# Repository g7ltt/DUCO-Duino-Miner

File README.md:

# DUCO/Duino-Miner

Here you will find designs for DUCO/DuinoCoin mining rigs based on various microcontrollers. All drawings are in Eagle format.

# 5DN

Uses a Wemos D1 and 5 arduino Nano's. I2C communications between the Wemos and the Nano's with the Wemos handling the network connection via WiFi. An LCD can be added for diagnostic output adn the boards can be "stacked" via the I2C bus. When stacked only a single Wemos is required. Uses code by Ricuan and JK Rolling

# 16-01

Uses 16 ESP-01 modules in one of 2 configurations; I2C Master/Slave mode or WiFi only. In I2C mode uses 1 of the ESP-01's as a Master talking to 15 slaves. wiFi only uses the WiFi radio on all the devices.

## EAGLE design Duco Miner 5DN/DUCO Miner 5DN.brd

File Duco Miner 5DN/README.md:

# Duco Miner 5DN
Arduino Nano (ATMEGA328) and Wemos D1 (ESP8266) based DUCO/Duino Coin miner. Uses a Wemos D1 as an I2C master controlling the 5 Nano I2C slaves. WiFi/Network handled by the Wemos microcontroller.

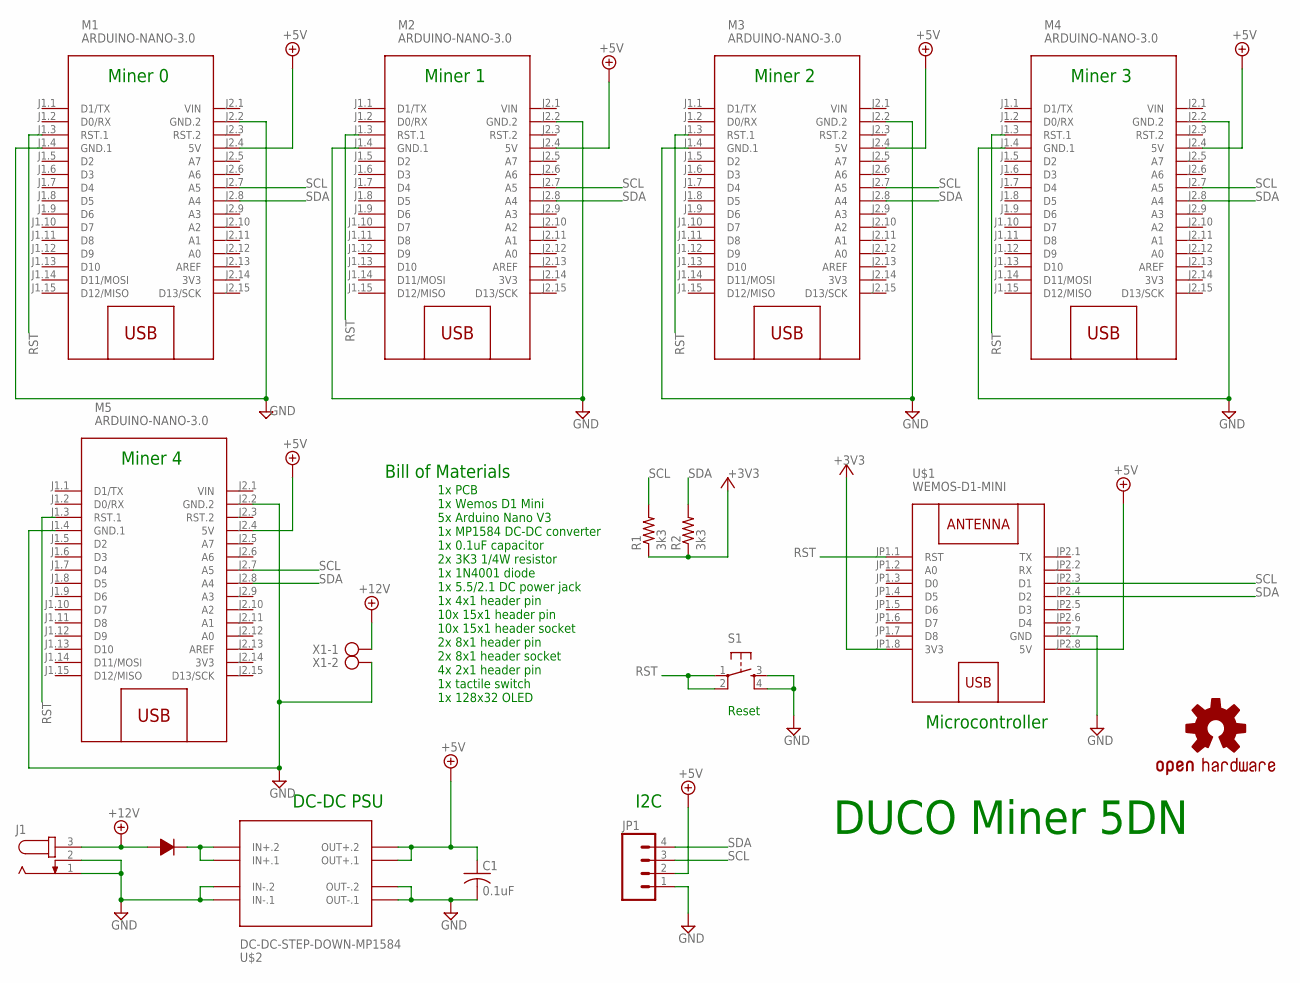
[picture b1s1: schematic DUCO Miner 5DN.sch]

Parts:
C1: 0.1uF; C025-025X050
J1: JACK-PLUG1; SPC4078
JP1: M04PTH; 1X04
LOGO1: OSHW-LOGOS; OSHW-LOGO-S
M1, M2, M3, M4, M5: ARDUINO-NANO-3.0
R1, R2: 3k3; 0204/7
S1: TAC_SWITCHPTH; TACTILE-PTH
U$1: WEMOS-D1-MINI
U$2: DC-DC-STEP-DOWN-MP1584
U$4: 1N4001; DIODE-12.70
X1: AK300/2

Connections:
3V3: M1.J2.14 (3V3), M2.J2.14 (3V3), M3.J2.14 (3V3), M4.J2.14 (3V3), M5.J2.14 (3V3)
+3V3: R1.1, R2.1, U$1.JP1.8 (3V3)
+5V: C1.1, JP1.2, M1.J2.4 (5V), M2.J2.4 (5V), M3.J2.4 (5V), M4.J2.4 (5V), M5.J2.4 (5V), U$1.JP2.8 (5V), U$2.OUT+.1, U$2.OUT+.2
+12V: J1.3, U$4.P$1, X1.1
GND: C1.2, J1.1, J1.2, JP1.1, M1.J1.4 (GND.1), M1.J2.2 (GND.2), M2.J1.4 (GND.1), M2.J2.2 (GND.2), M3.J1.4 (GND.1), M3.J2.2 (GND.2), M4.J1.4 (GND.1), M4.J2.2 (GND.2), M5.J1.4 (GND.1), M5.J2.2 (GND.2), S1.3, S1.4, U$1.JP2.7 (GND), U$2.IN-.1, U$2.IN-.2, U$2.OUT-.1, U$2.OUT-.2, X1.2
unnamed: U$2.IN+.1, U$2.IN+.2, U$4.P$2
RST: M1.J1.3 (RST.1), M2.J1.3 (RST.1), M3.J1.3 (RST.1), M4.J1.3 (RST.1), M5.J1.3 (RST.1), S1.1, S1.2, U$1.JP1.1 (RST)
SCL: JP1.3, M1.J2.7 (A5), M2.J2.7 (A5), M3.J2.7 (A5), M4.J2.7 (A5), M5.J2.7 (A5), R1.2, U$1.JP2.3 (D1)
SDA: JP1.4, M1.J2.8 (A4), M2.J2.8 (A4), M3.J2.8 (A4), M4.J2.8 (A4), M5.J2.8 (A4), R2.2, U$1.JP2.4 (D2)
VIN: M1.J2.1 (VIN), M2.J2.1 (VIN), M3.J2.1 (VIN), M4.J2.1 (VIN), M5.J2.1 (VIN)

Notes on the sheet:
Miner 0
Miner 1
Miner 2
Miner 4
Miner 3
DUCO Miner 5DN
Microcontroller
DC-DC PSU
I2C
Bill of Materials
1x PCB 1x Wemos D1 Mini 5x Arduino Nano V3 1x MP1584 DC-DC converter 1x 0.1uF capacitor 2x 3K3 1/4W resistor 1x 1N4001 diode 1x 5.5/2.1 DC power jack 1x 4x1 header pin 10x 15x1 header pin 10x 15x1 header socket 2x 8x1 header pin 2x 8x1 header socket 4x 2x1 header pin 1x tactile switch 1x 128x32 OLED
Reset

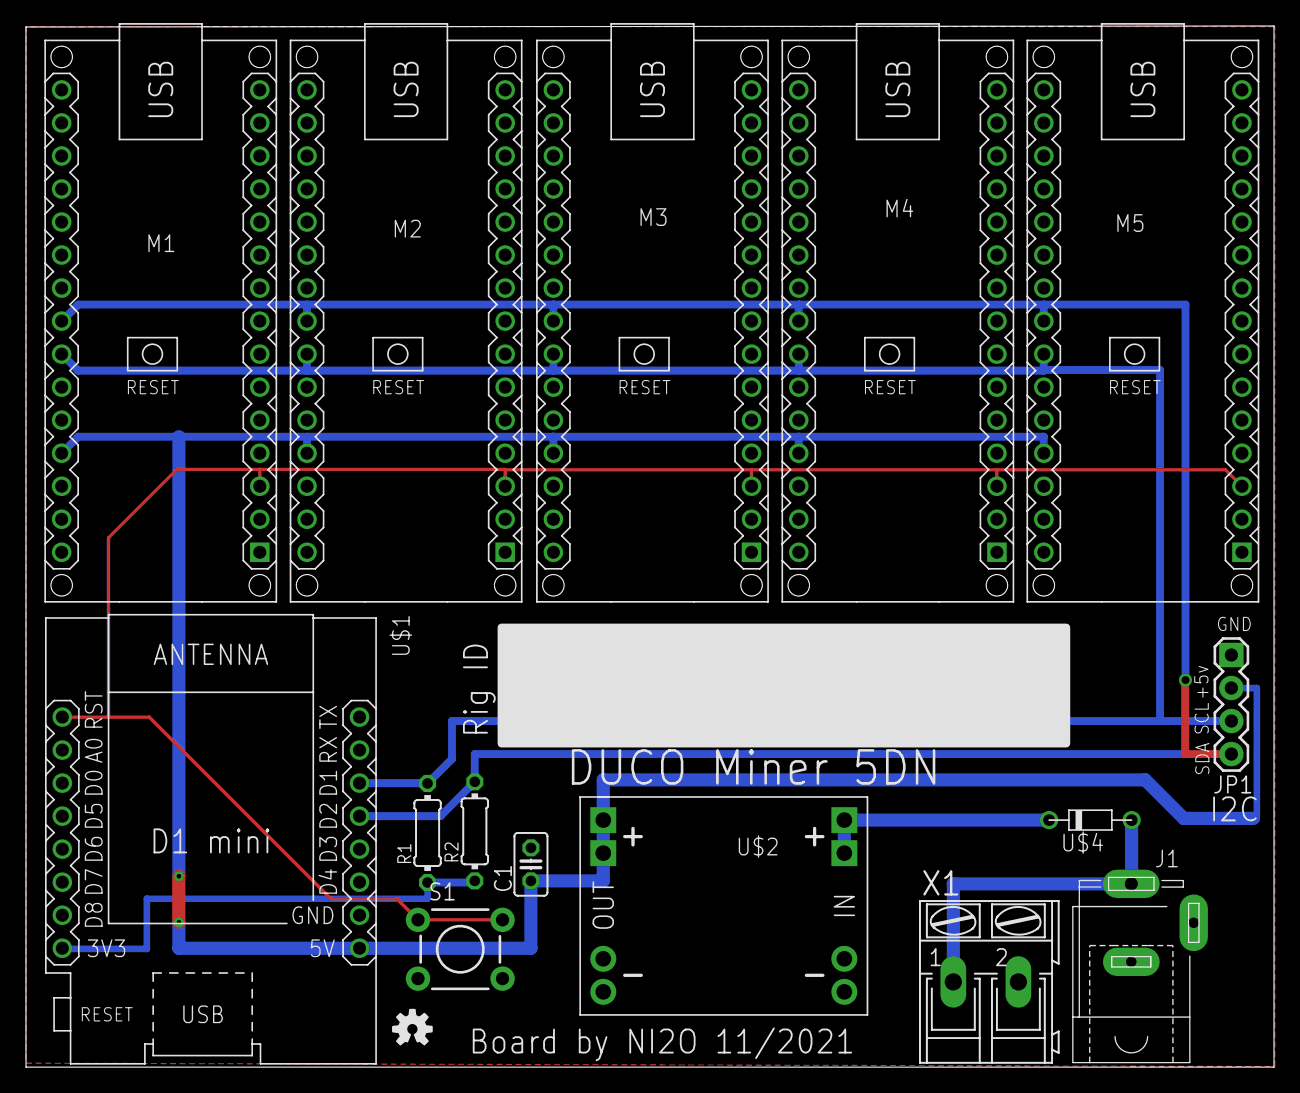
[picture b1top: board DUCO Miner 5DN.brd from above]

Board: 2 copper layers, 96.0 x 80.1 mm, 16 parts (0 on the bottom side), 10 nets.

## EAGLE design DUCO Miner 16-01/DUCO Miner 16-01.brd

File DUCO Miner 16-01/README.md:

# DUCO Miner 16-01

ESP-01 (ESP8266) based DUCO/Duino Coin miner. Uses a gang of ESP-01 Microcontrollers.

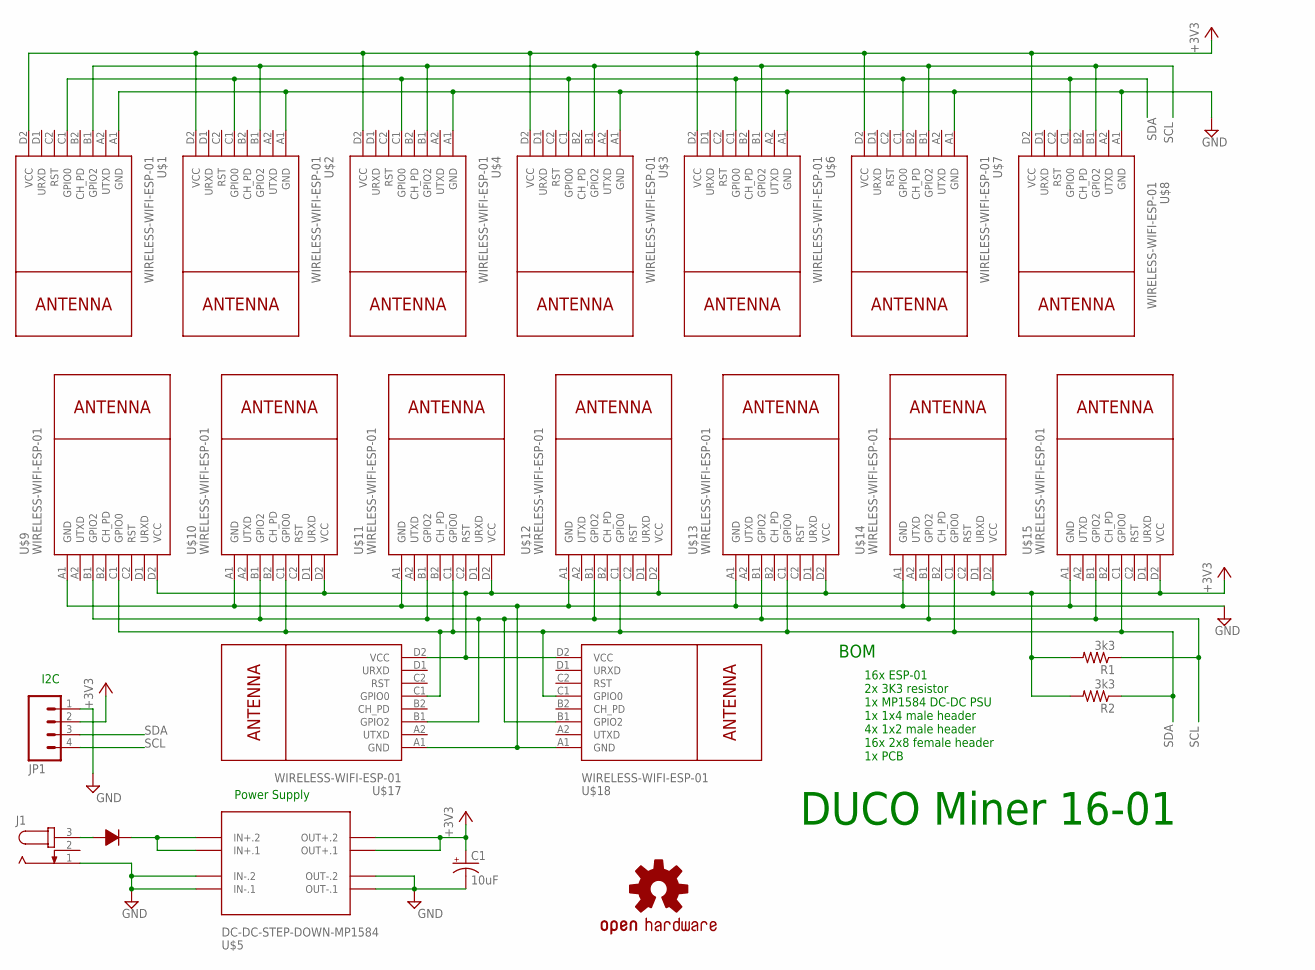
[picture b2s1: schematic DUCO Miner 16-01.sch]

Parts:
C1: 10uF; E2-5
J1: JACK-PLUG0; SPC4077
JP1: M04PTH; 1X04
LOGO1: OSHW-LOGOL; OSHW-LOGO-L
R1, R2: 3k3; 0204/7
U$1, U$2, U$3, U$4, U$6, U$7, U$8, U$9, U$10, U$11, U$12, U$13, U$14, U$15, U$17, U$18: WIRELESS-WIFI-ESP-01
U$5: DC-DC-STEP-DOWN-MP1584
U$16: 1N4001; DIODE-12.70

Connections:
+3V3: C1.+, JP1.2, R1.2, R2.2, U$1.D2 (VCC), U$2.D2 (VCC), U$3.D2 (VCC), U$4.D2 (VCC), U$5.OUT+.1, U$5.OUT+.2, U$6.D2 (VCC), U$7.D2 (VCC), U$8.D2 (VCC), U$9.D2 (VCC), U$10.D2 (VCC), U$11.D2 (VCC), U$12.D2 (VCC), U$13.D2 (VCC), U$14.D2 (VCC), U$15.D2 (VCC), U$17.D2 (VCC), U$18.D2 (VCC)
GND: C1.-, J1.1, JP1.1, U$1.A1 (GND), U$2.A1 (GND), U$3.A1 (GND), U$4.A1 (GND), U$5.IN-.1, U$5.IN-.2, U$5.OUT-.1, U$5.OUT-.2, U$6.A1 (GND), U$7.A1 (GND), U$8.A1 (GND), U$9.A1 (GND), U$10.A1 (GND), U$11.A1 (GND), U$12.A1 (GND), U$13.A1 (GND), U$14.A1 (GND), U$15.A1 (GND), U$17.A1 (GND), U$18.A1 (GND)
unnamed: J1.3, U$16.P$1
unnamed: U$5.IN+.1, U$5.IN+.2, U$16.P$2
SCL: JP1.4, R1.1, U$1.B1 (GPIO2), U$2.B1 (GPIO2), U$3.B1 (GPIO2), U$4.B1 (GPIO2), U$6.B1 (GPIO2), U$7.B1 (GPIO2), U$8.B1 (GPIO2), U$9.B1 (GPIO2), U$10.B1 (GPIO2), U$11.B1 (GPIO2), U$12.B1 (GPIO2), U$13.B1 (GPIO2), U$14.B1 (GPIO2), U$15.B1 (GPIO2), U$17.B1 (GPIO2), U$18.B1 (GPIO2)
SDA: JP1.3, R2.1, U$1.C1 (GPIO0), U$2.C1 (GPIO0), U$3.C1 (GPIO0), U$4.C1 (GPIO0), U$6.C1 (GPIO0), U$7.C1 (GPIO0), U$8.C1 (GPIO0), U$9.C1 (GPIO0), U$10.C1 (GPIO0), U$11.C1 (GPIO0), U$12.C1 (GPIO0), U$13.C1 (GPIO0), U$14.C1 (GPIO0), U$15.C1 (GPIO0), U$17.C1 (GPIO0), U$18.C1 (GPIO0)

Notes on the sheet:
DUCO Miner 16-01
Power Supply
I2C
BOM
16x ESP-01 2x 3K3 resistor 1x MP1584 DC-DC PSU 1x 1x4 male header 4x 1x2 male header 16x 2x8 female header 1x PCB

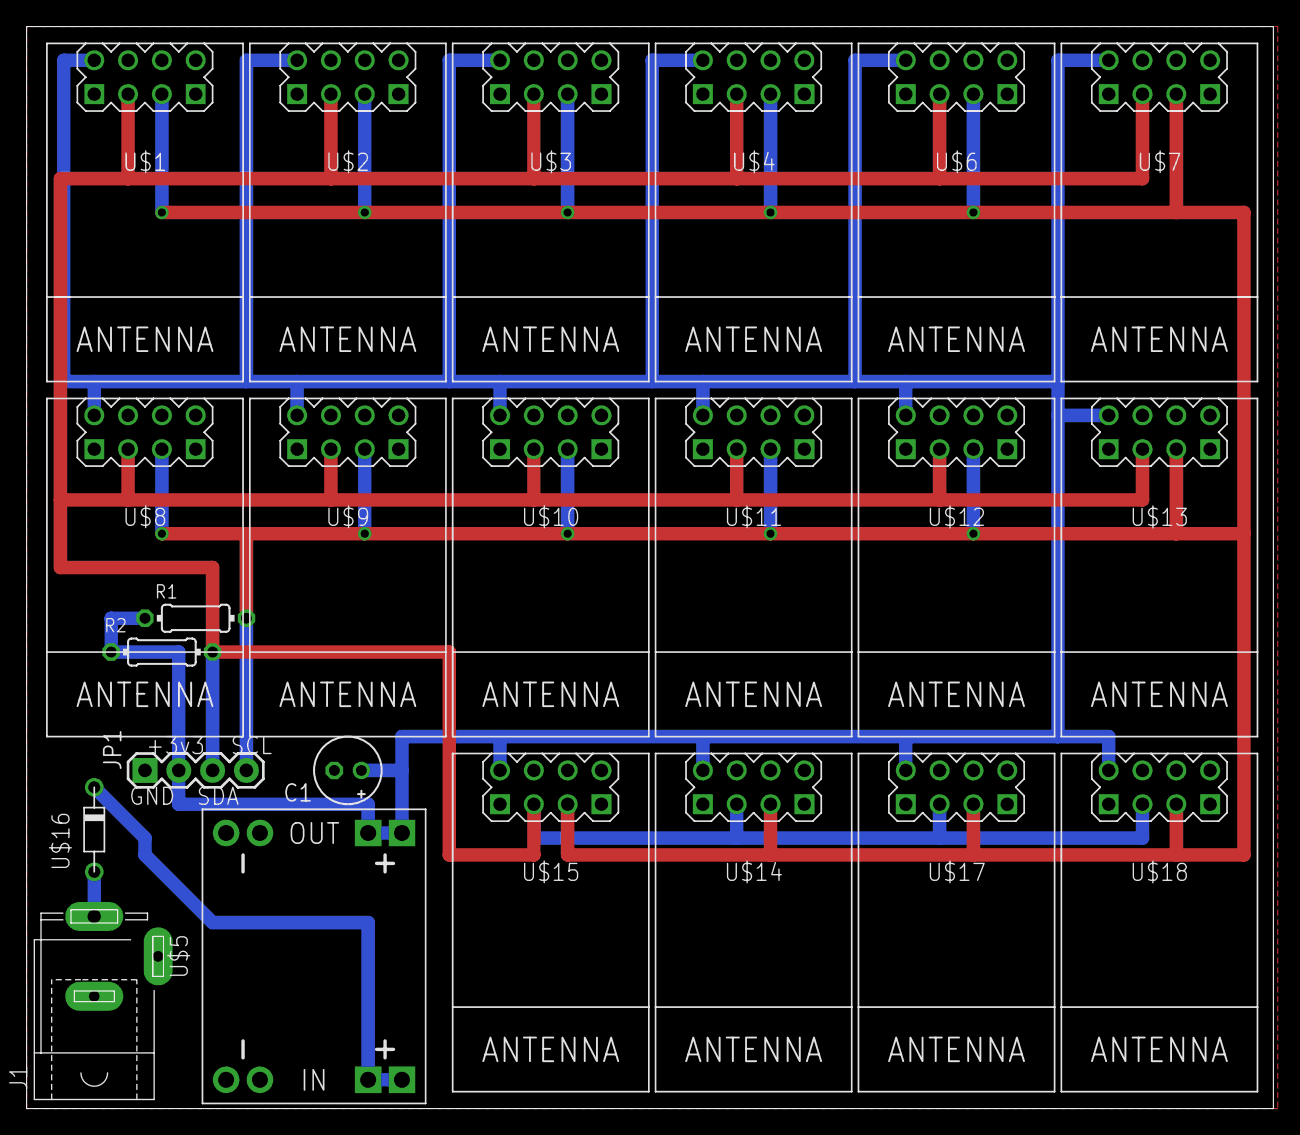
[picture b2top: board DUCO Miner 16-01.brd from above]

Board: 2 copper layers, 93.7 x 81.3 mm, 24 parts (1 on the bottom side), 6 nets.

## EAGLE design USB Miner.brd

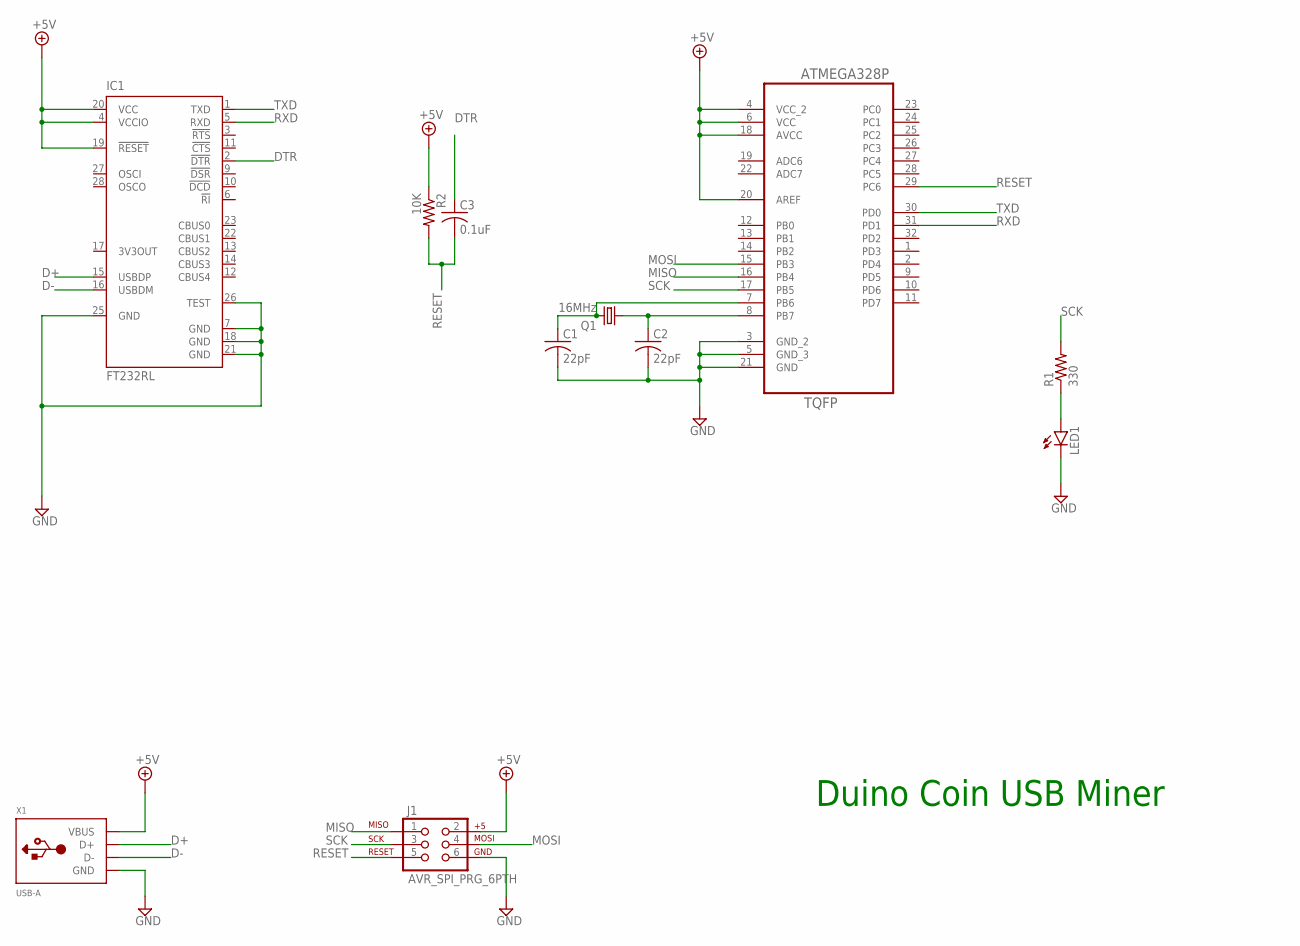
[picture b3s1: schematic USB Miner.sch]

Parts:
C1, C2: 22pF; C0805
C3: 0.1uF; C0805
IC1: FT232RL; SSOP28
J1: AVR_SPI_PRG_6PTH; 2X3
LED1: LEDCHIP-LED0805; CHIP-LED0805
Q1: 16MHz; CTS406
R1: 330; M0805
R2: 10K; M0805
U1: ATMEGA328P-AU; QFP80P900X900X120-32N
X1: USB-A; MOLEX_480371000

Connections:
+5V: IC1.4 (VCCIO), IC1.19 (!RESET), IC1.20 (VCC), J1.2, R2.1, U1.4 (VCC_2), U1.6 (VCC), U1.18 (AVCC), U1.20 (AREF), X1.1 (VBUS)
D+: IC1.15 (USBDP), X1.3 (D+)
D-: IC1.16 (USBDM), X1.2 (D-)
DTR: C3.1, IC1.2 (!DTR)
GND: C1.2, C2.2, IC1.7 (GND), IC1.18 (GND), IC1.21 (GND), IC1.25 (GND), IC1.26 (TEST), J1.6, LED1.C, U1.3 (GND_2), U1.5 (GND_3), U1.21 (GND), X1.4 (GND)
MISO: J1.1, U1.16 (PB4)
MOSI: J1.4, U1.15 (PB3)
unnamed: C2.1, Q1.1, U1.8 (PB7)
unnamed: C1.1, Q1.3 (2), U1.7 (PB6)
unnamed: LED1.A, R1.1
RESET: C3.2, J1.5, R2.2, U1.29 (PC6)
RXD: IC1.5 (RXD), U1.31 (PD1)
SCK: J1.3, R1.2, U1.17 (PB5)
TXD: IC1.1 (TXD), U1.30 (PD0)

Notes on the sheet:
Duino Coin USB Miner

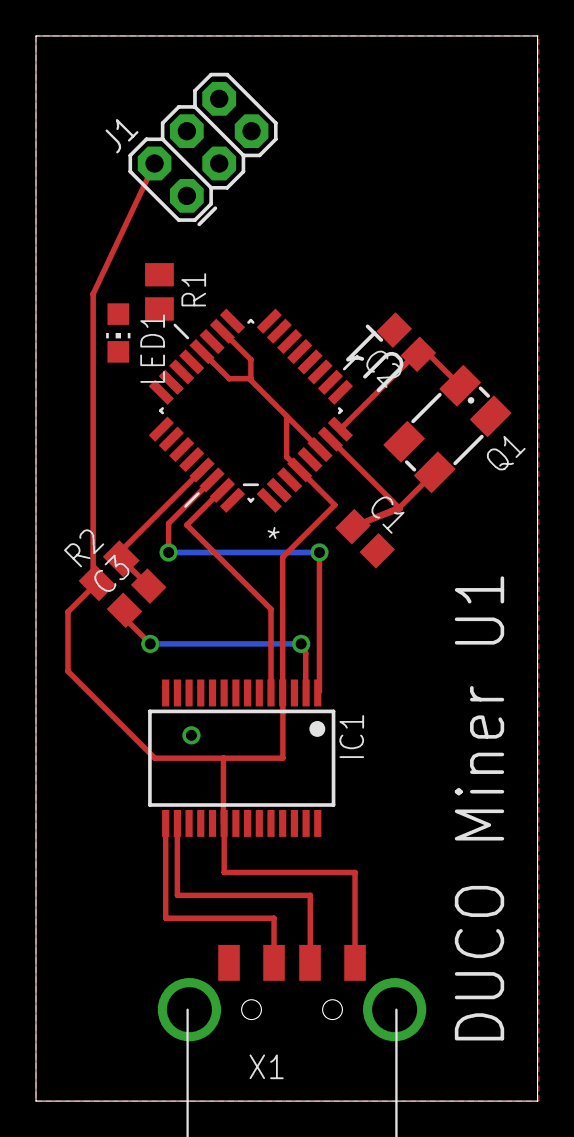
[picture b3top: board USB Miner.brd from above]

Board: 2 copper layers, 27.9 x 59.2 mm, 11 parts (0 on the bottom side), 14 nets.

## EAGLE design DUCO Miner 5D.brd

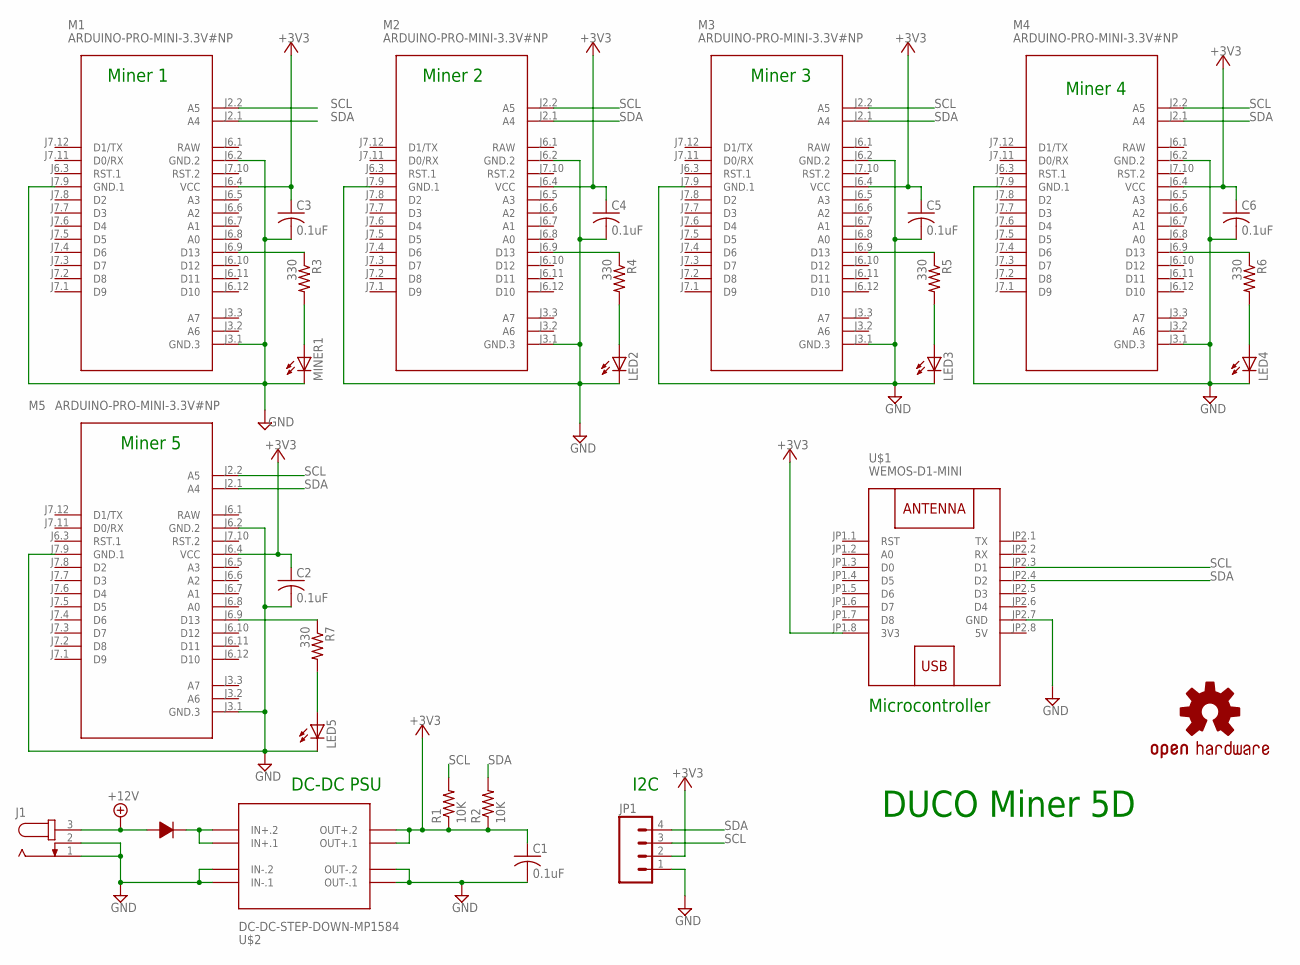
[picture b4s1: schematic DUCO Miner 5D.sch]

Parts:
C1, C2, C3, C4, C5, C6: 0.1uF; C025-025X050
J1: JACK-PLUG1; SPC4078
JP1: M04PTH; 1X04
LED2, LED3, LED4, LED5: LED3MM
LOGO1: OSHW-LOGOS; OSHW-LOGO-S
M1, M2, M3, M4, M5: ARDUINO-PRO-MINI-3.3V#NP; ARDUINO-PRO-MINI#NP
MINER1: LED3MM
R1, R2: 10K; 0204/7
R3, R4, R5, R6, R7: 330; 0204/7
U$1: WEMOS-D1-MINI
U$2: DC-DC-STEP-DOWN-MP1584
U$4: 1N4001; DIODE-12.70

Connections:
5V: U$1.JP2.8 (5V)
+3V3: C1.1, C2.1, C3.1, C4.1, C5.1, C6.1, JP1.2, M1.J6.4 (VCC), M2.J6.4 (VCC), M3.J6.4 (VCC), M4.J6.4 (VCC), M5.J6.4 (VCC), R1.1, R2.1, U$1.JP1.8 (3V3), U$2.OUT+.1, U$2.OUT+.2
+12V: J1.3, U$4.P$1
GND: C1.2, C2.2, C3.2, C4.2, C5.2, C6.2, J1.1, J1.2, JP1.1, LED2.K (C), LED3.K (C), LED4.K (C), LED5.K (C), M1.J3.1 (GND.3), M1.J6.2 (GND.2), M1.J7.9 (GND.1), M2.J3.1 (GND.3), M2.J6.2 (GND.2), M2.J7.9 (GND.1), M3.J3.1 (GND.3), M3.J6.2 (GND.2), M3.J7.9 (GND.1), M4.J3.1 (GND.3), M4.J6.2 (GND.2), M4.J7.9 (GND.1), M5.J3.1 (GND.3), M5.J6.2 (GND.2), M5.J7.9 (GND.1), MINER1.K (C), U$1.JP2.7 (GND), U$2.IN-.1, U$2.IN-.2, U$2.OUT-.1, U$2.OUT-.2
unnamed: U$2.IN+.1, U$2.IN+.2, U$4.P$2
unnamed: M1.J6.9 (D13), R3.1
unnamed: MINER1.A, R3.2
unnamed: M2.J6.9 (D13), R4.1
unnamed: LED2.A, R4.2
unnamed: M3.J6.9 (D13), R5.1
unnamed: LED3.A, R5.2
unnamed: M4.J6.9 (D13), R6.1
unnamed: LED4.A, R6.2
unnamed: M5.J6.9 (D13), R7.1
unnamed: LED5.A, R7.2
RAW: M1.J6.1 (RAW), M2.J6.1 (RAW), M3.J6.1 (RAW), M4.J6.1 (RAW), M5.J6.1 (RAW)
SCL: JP1.3, M1.J2.2 (A5), M2.J2.2 (A5), M3.J2.2 (A5), M4.J2.2 (A5), M5.J2.2 (A5), R1.2, U$1.JP2.3 (D1)
SDA: JP1.4, M1.J2.1 (A4), M2.J2.1 (A4), M3.J2.1 (A4), M4.J2.1 (A4), M5.J2.1 (A4), R2.2, U$1.JP2.4 (D2)

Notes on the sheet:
Miner 1
Miner 2
Miner 3
Miner 4
Miner 5
DUCO Miner 5D
Microcontroller
DC-DC PSU
I2C

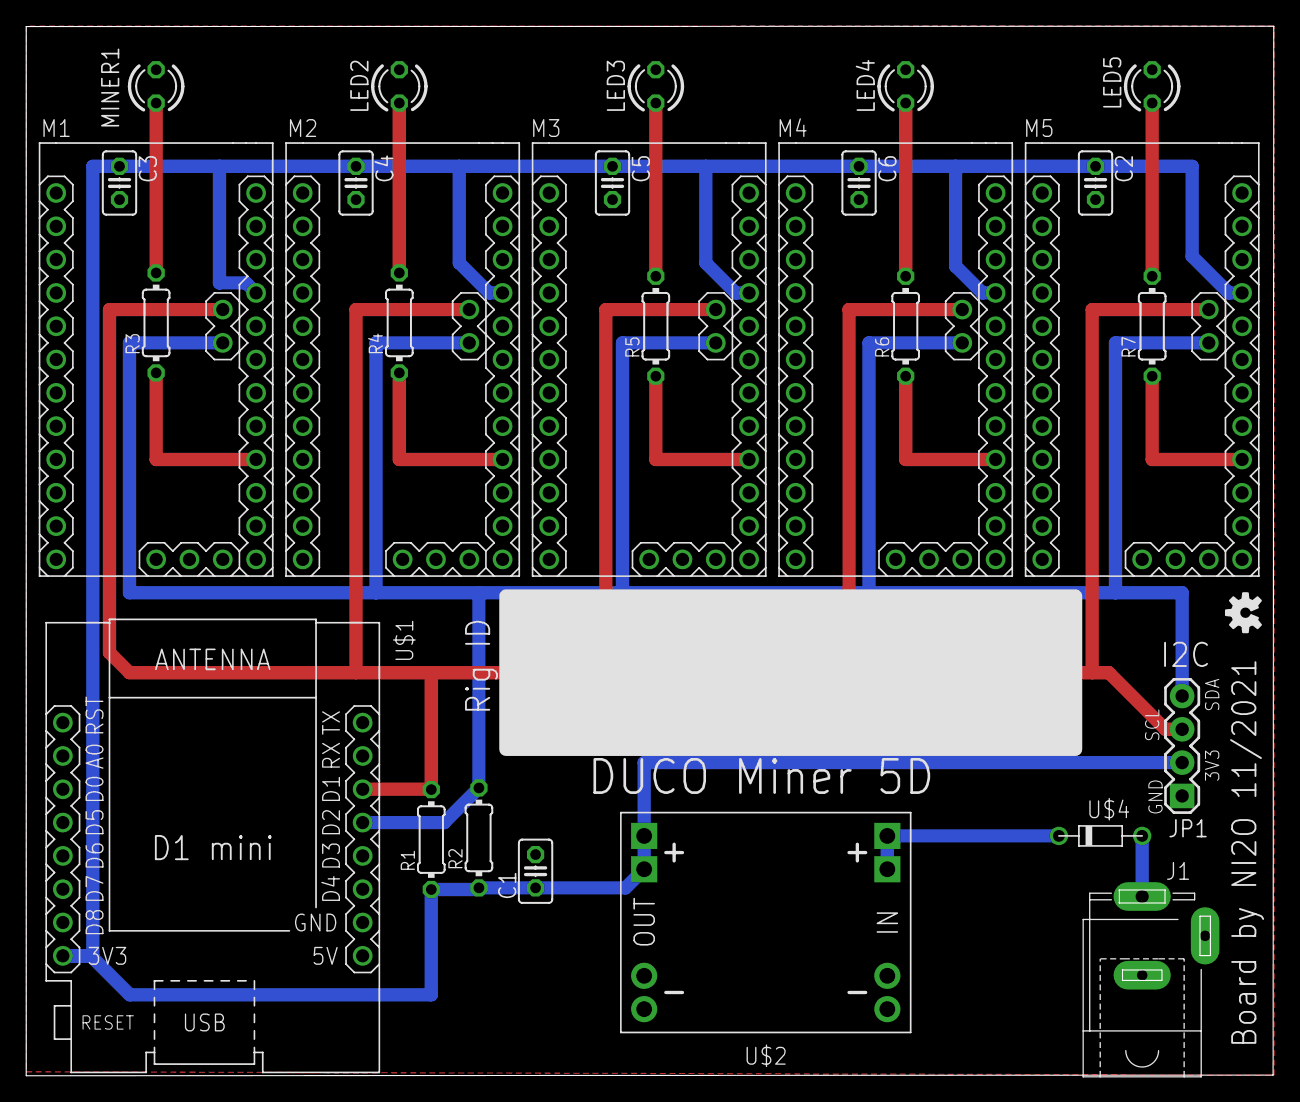
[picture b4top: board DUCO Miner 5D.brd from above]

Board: 2 copper layers, 95.1 x 80.0 mm, 29 parts (0 on the bottom side), 17 nets.

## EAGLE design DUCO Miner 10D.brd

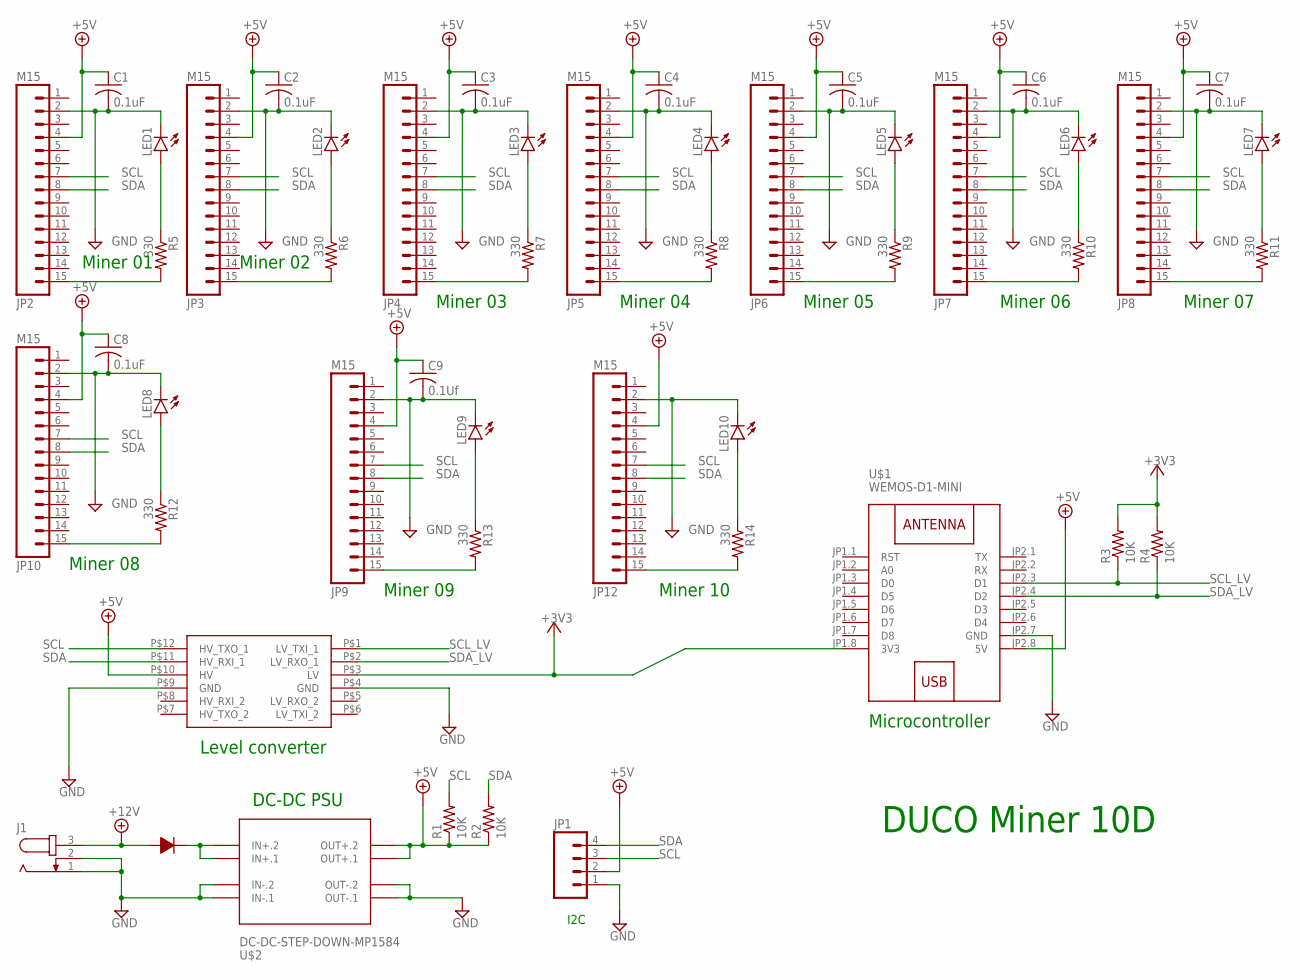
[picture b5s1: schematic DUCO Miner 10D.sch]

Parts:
C1, C2, C3, C4, C5, C6, C7, C8: 0.1uF; C025-025X050
C9: 0.1Uf; C025-025X050
J1: JACK-PLUG1; SPC4078
JP1: M04PTH; 1X04
JP2, JP3, JP4, JP5, JP6, JP7, JP8, JP9, JP10, JP12: M15; 1X15
LED1, LED2, LED3, LED4, LED5, LED6, LED7, LED8, LED9, LED10: LED3MM
R1, R2, R3, R4: 10K; 0204/7
R5, R6, R7, R8, R9, R10, R11, R12, R13, R14: 330; 0204/7
U$1: WEMOS-D1-MINI
U$2: DC-DC-STEP-DOWN-MP1584
U$3: LOGIC_LEVEL_CONVERTER
U$4: 1N4001; DIODE-12.70

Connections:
+3V3: R3.2, R4.2, U$1.JP1.8 (3V3), U$3.P$3 (LV)
+5V: C1.1, C2.1, C3.1, C4.1, C5.1, C6.1, C7.1, C8.1, C9.1, JP1.2, JP2.4, JP3.4, JP4.4, JP5.4, JP6.4, JP7.4, JP8.4, JP9.4, JP10.4, JP12.4, R1.1, R2.1, U$1.JP2.8 (5V), U$2.OUT+.1, U$2.OUT+.2, U$3.P$10 (HV)
+12V: J1.3, U$4.P$1
GND: C1.2, C2.2, C3.2, C4.2, C5.2, C6.2, C7.2, C8.2, C9.2, J1.1, J1.2, JP1.1, JP2.2, JP3.2, JP4.2, JP5.2, JP6.2, JP7.2, JP8.2, JP9.2, JP10.2, JP12.2, LED1.K (C), LED2.K (C), LED3.K (C), LED4.K (C), LED5.K (C), LED6.K (C), LED7.K (C), LED8.K (C), LED9.K (C), LED10.K (C), U$1.JP2.7 (GND), U$2.IN-.1, U$2.IN-.2, U$2.OUT-.1, U$2.OUT-.2, U$3.P$4 (GND), U$3.P$9 (GND)
unnamed: JP2.15, R5.2
unnamed: U$2.IN+.1, U$2.IN+.2, U$4.P$2
unnamed: LED1.A, R5.1
unnamed: JP12.15, R14.2
unnamed: JP3.15, R6.2
unnamed: LED2.A, R6.1
unnamed: JP9.15, R13.2
unnamed: JP4.15, R7.2
unnamed: LED3.A, R7.1
unnamed: JP10.15, R12.2
unnamed: JP5.15, R8.2
unnamed: LED4.A, R8.1
unnamed: JP6.15, R9.2
unnamed: LED5.A, R9.1
unnamed: JP7.15, R10.2
unnamed: LED6.A, R10.1
unnamed: LED8.A, R12.1
unnamed: JP8.15, R11.2
unnamed: LED7.A, R11.1
unnamed: LED9.A, R13.1
unnamed: LED10.A, R14.1
SCL: JP1.3, JP2.7, JP3.7, JP4.7, JP5.7, JP6.7, JP7.7, JP8.7, JP9.7, JP10.7, JP12.7, R1.2, U$3.P$12 (HV_TXO_1)
SCL_LV: R3.1, U$1.JP2.3 (D1), U$3.P$1 (LV_TXI_1)
SDA: JP1.4, JP2.8, JP3.8, JP4.8, JP5.8, JP6.8, JP7.8, JP8.8, JP9.8, JP10.8, JP12.8, R2.2, U$3.P$11 (HV_RXI_1)
SDA_LV: R4.1, U$1.JP2.4 (D2), U$3.P$2 (LV_RXO_1)

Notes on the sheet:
Miner 01
DUCO Miner 10D
Level converter
Microcontroller
DC-DC PSU
Miner 02
I2C
Miner 03
Miner 04
Miner 05
Miner 06
Miner 07
Miner 08
Miner 09
Miner 10

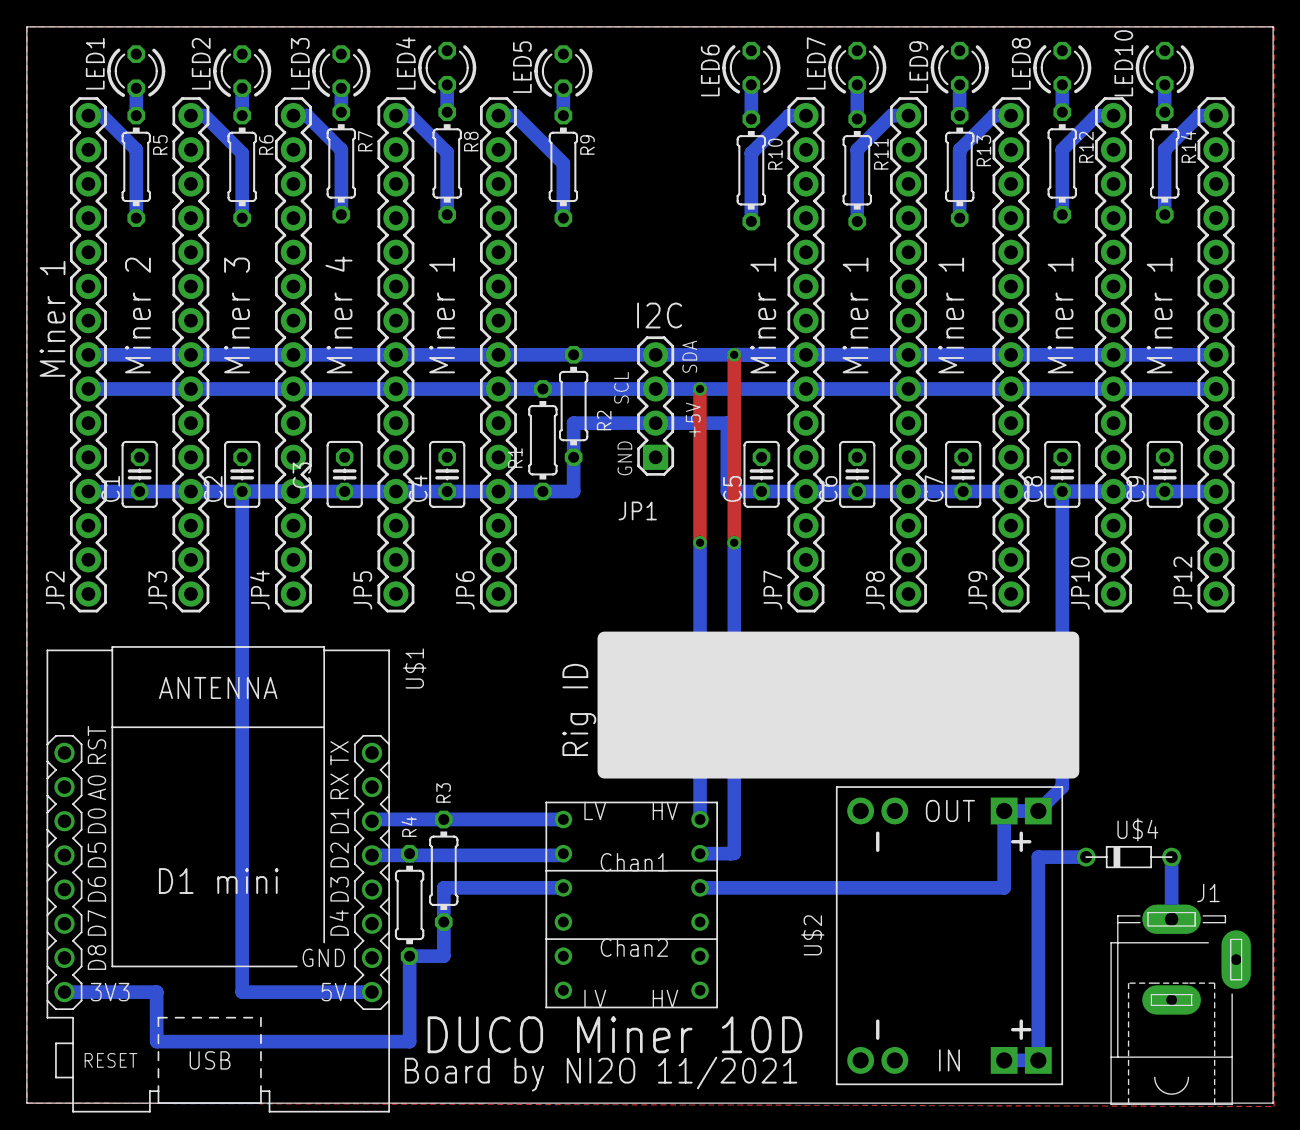
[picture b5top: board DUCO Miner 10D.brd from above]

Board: 2 copper layers, 92.6 x 80.0 mm, 49 parts (0 on the bottom side), 29 nets.

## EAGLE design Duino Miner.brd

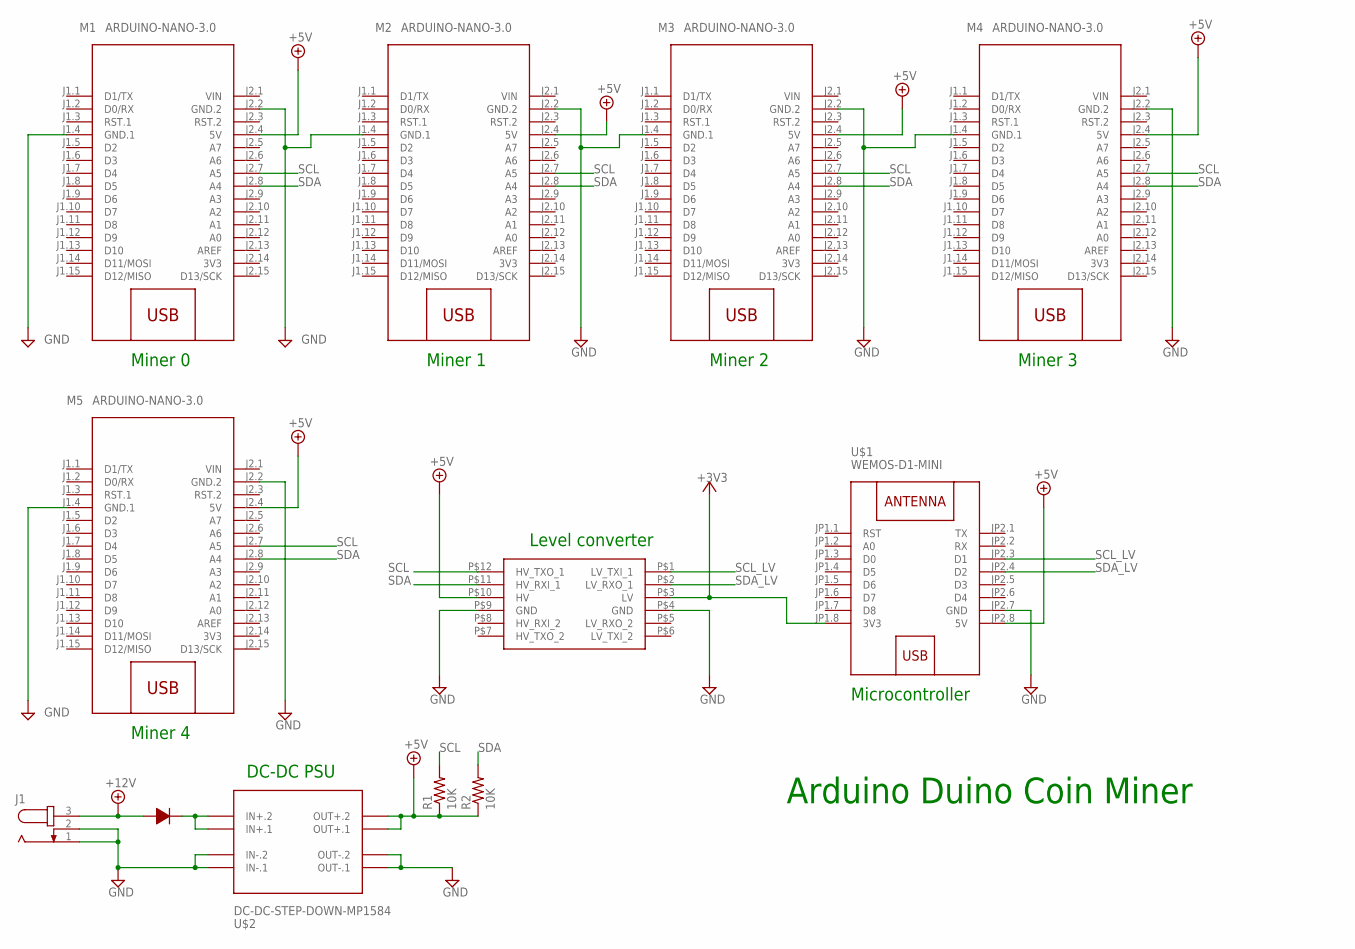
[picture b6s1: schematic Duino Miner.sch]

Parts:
J1: JACK-PLUG1; SPC4078
M1, M2, M3, M4, M5: ARDUINO-NANO-3.0
R1, R2: 10K; 0204/7
U$1: WEMOS-D1-MINI
U$2: DC-DC-STEP-DOWN-MP1584
U$3: LOGIC_LEVEL_CONVERTER
U$4: 1N4001; DIODE-12.70

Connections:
3V3: M1.J2.14 (3V3), M2.J2.14 (3V3), M3.J2.14 (3V3), M4.J2.14 (3V3), M5.J2.14 (3V3)
+3V3: U$1.JP1.8 (3V3), U$3.P$3 (LV)
+5V: M1.J2.4 (5V), M2.J2.4 (5V), M3.J2.4 (5V), M4.J2.4 (5V), M5.J2.4 (5V), R1.1, R2.1, U$1.JP2.8 (5V), U$2.OUT+.1, U$2.OUT+.2, U$3.P$10 (HV)
+12V: J1.3, U$4.P$1
GND: J1.1, J1.2, M1.J1.4 (GND.1), M1.J2.2 (GND.2), M2.J1.4 (GND.1), M2.J2.2 (GND.2), M3.J1.4 (GND.1), M3.J2.2 (GND.2), M4.J1.4 (GND.1), M4.J2.2 (GND.2), M5.J1.4 (GND.1), M5.J2.2 (GND.2), U$1.JP2.7 (GND), U$2.IN-.1, U$2.IN-.2, U$2.OUT-.1, U$2.OUT-.2, U$3.P$4 (GND), U$3.P$9 (GND)
unnamed: U$2.IN+.1, U$2.IN+.2, U$4.P$2
SCL: M1.J2.7 (A5), M2.J2.7 (A5), M3.J2.7 (A5), M4.J2.7 (A5), M5.J2.7 (A5), R1.2, U$3.P$12 (HV_TXO_1)
SCL_LV: U$1.JP2.3 (D1), U$3.P$1 (LV_TXI_1)
SDA: M1.J2.8 (A4), M2.J2.8 (A4), M3.J2.8 (A4), M4.J2.8 (A4), M5.J2.8 (A4), R2.2, U$3.P$11 (HV_RXI_1)
SDA_LV: U$1.JP2.4 (D2), U$3.P$2 (LV_RXO_1)
VIN: M1.J2.1 (VIN), M2.J2.1 (VIN), M3.J2.1 (VIN), M4.J2.1 (VIN), M5.J2.1 (VIN)

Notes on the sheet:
Miner 0
Miner 1
Miner 2
Miner 3
Miner 4
Arduino Duino Coin Miner
Level converter
Microcontroller
DC-DC PSU

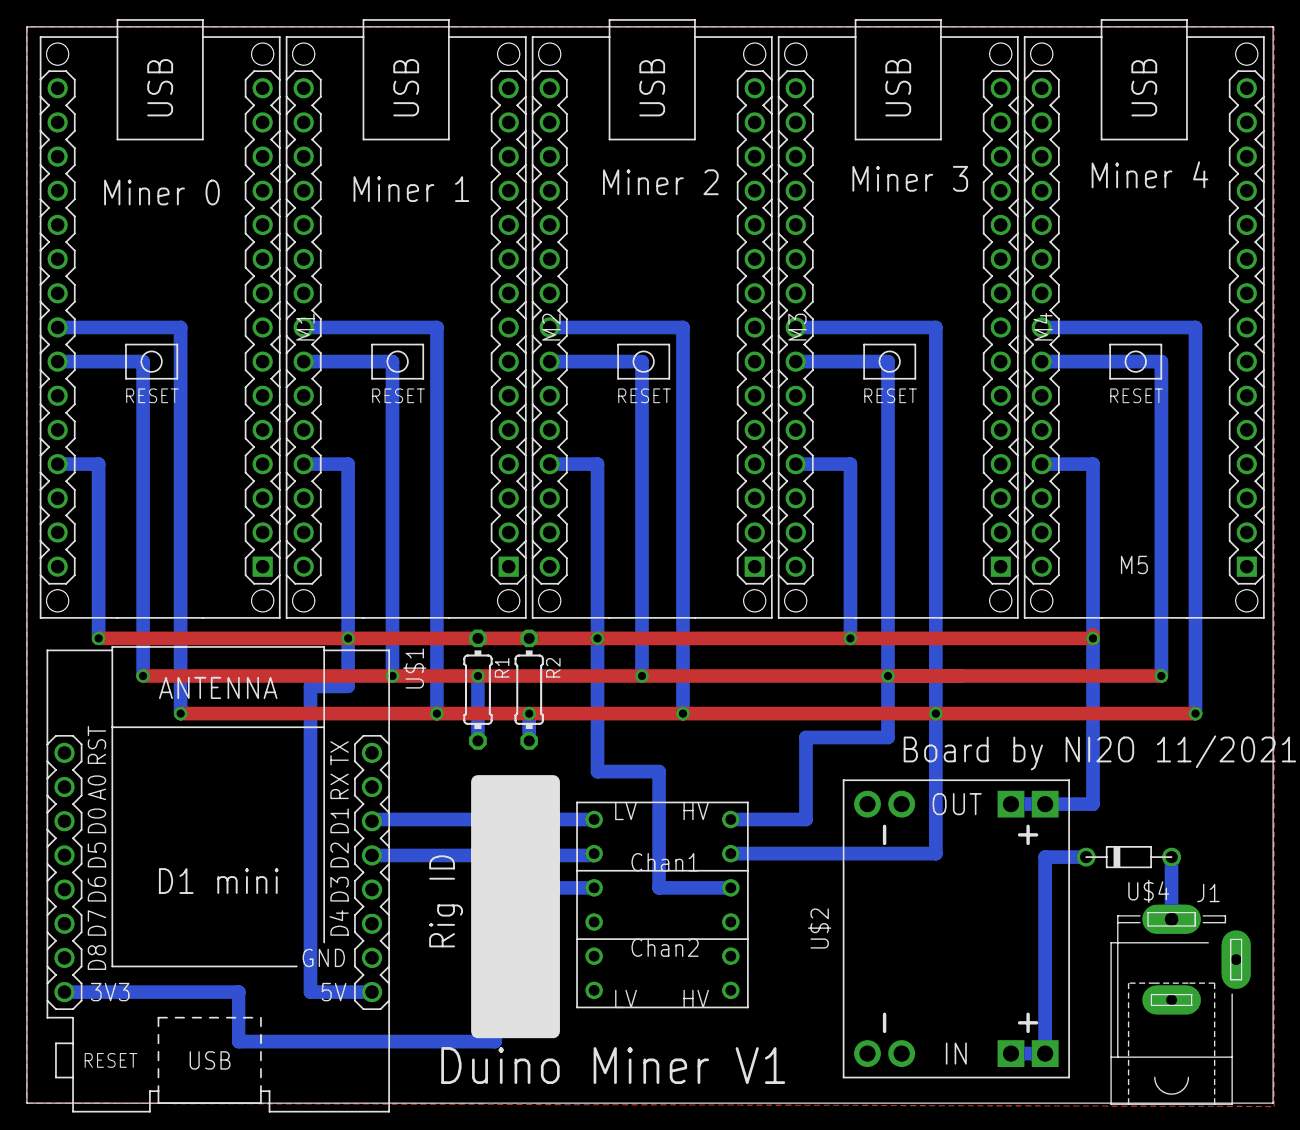
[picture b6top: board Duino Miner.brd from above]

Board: 2 copper layers, 92.6 x 80.0 mm, 12 parts (0 on the bottom side), 11 nets.

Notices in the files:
parts and their libraries:
diy-modules: Released under the Creative Commons Attribution 4.0 International License: http://creativecommons.org/licenses/by/4.0
SparkFun-Boards: Licensing: Creative Commons ShareAlike 4.0 International - https://creativecommons.org/licenses/by-sa/4.0
